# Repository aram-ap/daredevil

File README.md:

### Project Overview

A concise summary of the problem, goals, scope, and tools behind this project.

#### Problem Statement

A computer-vision based system which uses a depth camera and a set of vibration motors along each wrist to identify obstacles and help the visually impaired avoid physical dangers.

This project will utilize an Intel RealSense Depth Camera, NVIDIA Jetson Orin Nano, ESP32 microcontrollers, small vibration motors, and Batteries for its hardware. Software will be developed to utilize the camera system to identify obstacles. Vibration motors will change intensity and pattern for giving general direction and/or identify specific dangers.

#### Project Goals

The goal by the end of class is to have a working software + hardware proof of concept that can reliably detect obstacles, provide haptic feedback to nearest obstacles, utilize variable vibration intensities, and be fully wearable.

#### Scope of Work

This will be a self-contained device. Self-powered and can be ran completely isolated.

#### Tech Stack

TBD

#### Hardware

Hardware design files live in [`hardware/`](hardware/). All PCB work is done in **KiCad 10**, and enclosures are modeled in **Autodesk Fusion**. See the [hardware README](hardware/README.md) for full details.

```
hardware/
+-- README.md
+-- models/                        3D models for enclosures
|   +-- Wrist Module/
|       +-- Wrist_Module_Enclosure.f3z    Fusion archive (editable source)
|       +-- Wrist Module Enclosure.3mf    Print-ready model (open in a slicer)
|       +-- enclosure.png                 Assembled render
|       +-- enclosure_exploded.png        Exploded render
+-- wrist_module/                  KiCad project for the wrist haptic board
    +-- wrist_module.kicad_pro     Project file (open this in KiCad)
    +-- wrist_module.kicad_sch     Schematic
    +-- wrist_module.kicad_pcb     PCB layout
    +-- wrist_module.kicad_prl     Local KiCad UI settings (per user)
    +-- Prints/                    Exported schematic and board renders
    |   +-- wrist_module.pdf       Schematic (PDF)
    |   +-- wrist_schematic.png    Schematic (PNG, made from the PDF)
    |   +-- wrist_module.png       Front render
    |   +-- pcb_traces.png         PCB layout showing copper traces
    |   +-- wrist_module_back.png  Back render
    +-- Library/                   Third-party symbols and footprints
        +-- 113991054/             Seeed XIAO ESP32C3 symbol, footprint, and 3D model
        +-- OPL_Kicad_Library-master/  Seeed Open Parts Library
```

##### Wrist Module

The wrist module is a small battery-powered board worn on each wrist. It drives up to five vibration motors that signal the direction and type of nearby obstacles.

| Schematic | PCB (front) | PCB (traces) |
| --- | --- | --- |
|  |  |  |

| Part | Purpose |
| --- | --- |
| Seeed XIAO ESP32-C3 | Microcontroller; controls motor intensity and patterns |
| ULN2003A | Darlington driver array that switches the motors |
| 5 x motor connectors (MOT 1-5) | Vibration motor outputs, each with a 1N5819 flyback diode |
| Battery connector (BATT CONN) | Battery power input |
| PWR SW (SPDT) | Main power switch |
| TOGG BTN | User push button |
| PWR LED | Power indicator |

To open the project, open `hardware/wrist_module/wrist_module.kicad_pro` in KiCad 10. If symbols or footprints show as missing, add the libraries under `hardware/wrist_module/Library/` in **Preferences -> Manage Symbol/Footprint Libraries** (as project-specific libraries).

The board is housed in a two-part 3D-printed enclosure (base and lid, fastened with four cap screws that also hold the PCB). The lid has openings for the push button and power LED, and the base has side cutouts for the connectors and switch. The editable Fusion source (`.f3z`) and a print-ready `.3mf` are in [`hardware/models/Wrist Module/`](hardware/models/Wrist%20Module/).

| Enclosure (assembled) | Enclosure (exploded) |
| --- | --- |
|  |  |

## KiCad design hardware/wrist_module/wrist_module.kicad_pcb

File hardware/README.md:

# Hardware

Hardware design files for **DareDevil**, a wearable obstacle-detection system for the visually impaired. A depth camera and an NVIDIA Jetson Orin Nano detect obstacles, and a module on each wrist gives haptic feedback through vibration motors. See the [project README](../README.md) for the full overview.

All PCB work here is done in **KiCad 10**. Enclosures are modeled in **Autodesk Fusion** and exported for 3D printing.

**Author:** Aram Aprahamian ([aapraham@ucsc.edu](mailto:aapraham@ucsc.edu))

## Directory layout

```
hardware/
├── README.md
├── models/                        3D models for enclosures
│   └── Wrist Module/
│       ├── Wrist_Module_Enclosure.f3z    Fusion archive (editable source)
│       ├── Wrist Module Enclosure.3mf    Print-ready model (open in a slicer)
│       ├── enclosure.png                 Assembled render
│       └── enclosure_exploded.png        Exploded render
└── wrist_module/                  KiCad project for the wrist haptic board
    ├── wrist_module.kicad_pro     Project file (open this in KiCad)
    ├── wrist_module.kicad_sch     Schematic
    ├── wrist_module.kicad_pcb     PCB layout
    ├── wrist_module.kicad_prl     Local KiCad UI settings (per user)
    ├── Prints/                    Exported schematic and board renders
    │   ├── wrist_module.pdf       Schematic (PDF)
    │   ├── wrist_schematic.png    Schematic (PNG, made from the PDF)
    │   ├── wrist_module.png       Front render
    │   ├── pcb_traces.png         PCB layout showing copper traces
    │   └── wrist_module_back.png  Back render
    ├── Library/                   Third-party symbols and footprints
    │   ├── 113991054/             Seeed XIAO ESP32C3 symbol, footprint, and 3D model
    │   └── OPL_Kicad_Library-master/  Seeed Open Parts Library
```

## wrist_module

The wrist module is a small battery-powered board worn on each wrist. It drives up to five vibration motors that signal the direction and type of nearby obstacles.

| Schematic | PCB (front) | PCB (traces) |
| --- | --- | --- |
|  |  |  |

Main parts:

| Part | Purpose |
| --- | --- |
| Seeed XIAO ESP32-C3 | Microcontroller; controls motor intensity and patterns |
| ULN2003A | Darlington driver array that switches the motors |
| 5 x motor connectors (MOT 1–5) | Vibration motor outputs, each with a 1N5819 flyback diode |
| Battery connector (BATT CONN) | Battery power input |
| PWR SW (SPDT) | Main power switch |
| TOGG BTN | User push button |
| PWR LED | Power indicator |

### Enclosure

The board sits in a two-part 3D-printed enclosure: an open base and a flat lid, fastened together with four socket-head cap screws that also hold the PCB in place. The lid has openings for the push button (TOGG BTN) and the power LED, and the base has side cutouts for the board's connectors and switch.

| Assembled | Exploded |
| --- | --- |
|  |  |

- `models/Wrist Module/Wrist_Module_Enclosure.f3z`: editable source. Open it in Fusion with **File -> Open -> Open from my computer**.
- `models/Wrist Module/Wrist Module Enclosure.3mf`: print-ready model. Load it into a slicer (Bambu Studio, PrusaSlicer, Cura, etc.).

### Opening the project

1. Open `wrist_module/wrist_module.kicad_pro` in KiCad 10.
2. If symbols or footprints show as missing, add the libraries under `wrist_module/Library/` in **Preferences -> Manage Symbol/Footprint Libraries** (as project-specific libraries).

### Notes

- Everything in `Prints/` is exported from KiCad, and the enclosure renders and `.3mf` are exported from Fusion. Re-export them after changing the design so they stay current.
- To regenerate the schematic PNG from the PDF (needs ImageMagick and Ghostscript):
  `magick -density 300 wrist_module/Prints/wrist_module.pdf -background white -alpha remove -alpha off wrist_module/Prints/wrist_schematic.png`

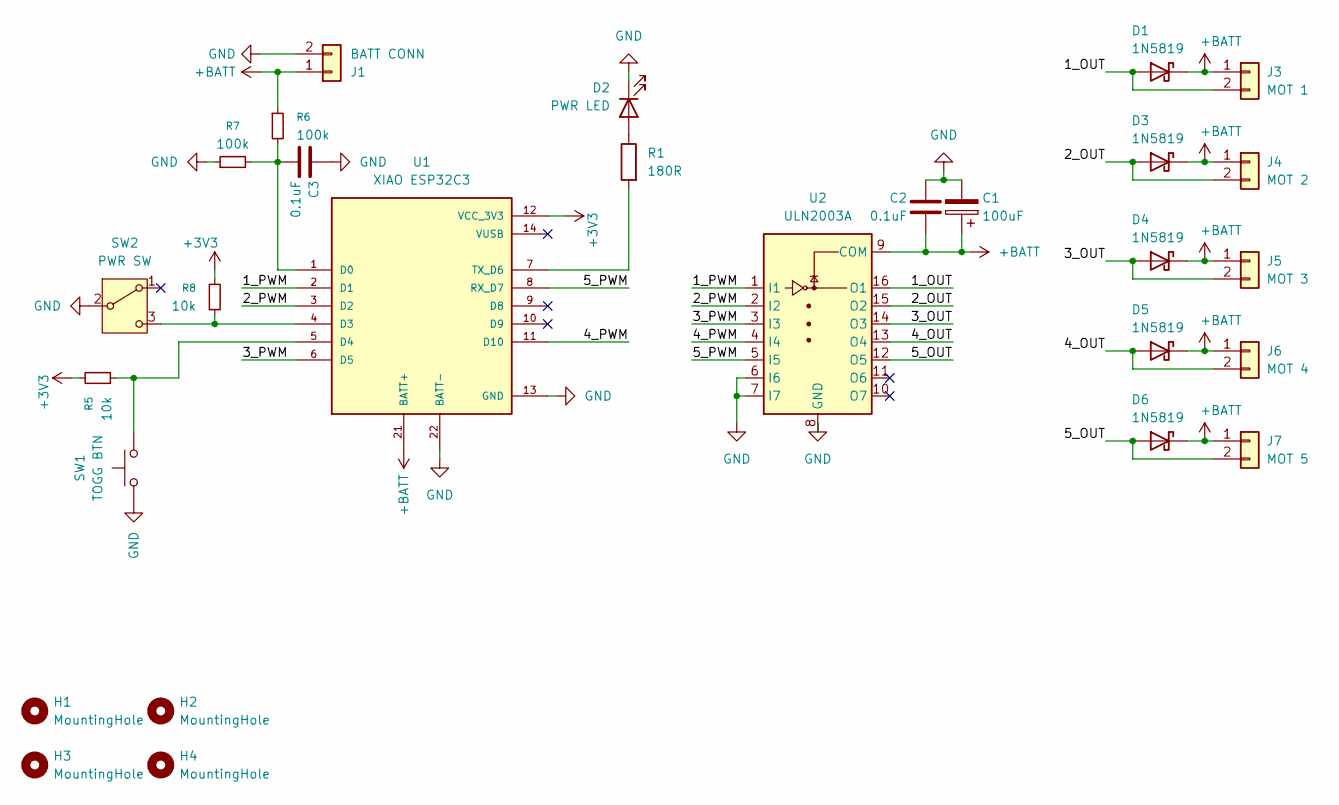
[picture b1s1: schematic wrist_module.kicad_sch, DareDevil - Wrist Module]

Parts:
C1: 100uF; CP_Radial_D8.0mm_P2.50mm
C2, C3: 0.1uF; C_Disc_D3.8mm_W2.6mm_P2.50mm
D1, D3, D4, D5, D6: 1N5819; D_DO-41_SOD81_P10.16mm_Horizontal
D2: PWR LED; LED_D5.0mm
H1, H2, H3, H4: MountingHole; MountingHole_2.2mm_M2_ISO7380
J1: BATT CONN; JST_PH_B2B-PH-K_1x02_P2.00mm_Vertical
J3: MOT 1; JST_PH_B2B-PH-K_1x02_P2.00mm_Vertical
J4: MOT 2; JST_PH_B2B-PH-K_1x02_P2.00mm_Vertical
J5: MOT 3; JST_PH_B2B-PH-K_1x02_P2.00mm_Vertical
J6: MOT 4; JST_PH_B2B-PH-K_1x02_P2.00mm_Vertical
J7: MOT 5; JST_PH_B2B-PH-K_1x02_P2.00mm_Vertical
R1: 180R; R_Axial_DIN0207_L6.3mm_D2.5mm_P7.62mm_Horizontal
R5, R8: 10k; R_Axial_DIN0207_L6.3mm_D2.5mm_P7.62mm_Horizontal
R6, R7: 100k; R_Axial_DIN0207_L6.3mm_D2.5mm_P7.62mm_Horizontal
SW1: TOGG BTN; SW_PUSH_6mm
SW2: PWR SW; JST_PH_B3B-PH-K_1x03_P2.00mm_Vertical
U1: XIAO ESP32C3; XIAO-ESP32-C3-DIP-SMD; PARTREV 23/05/2022
U2: ULN2003A; DIP-16_W7.62mm_LongPads

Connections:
+3V3: R5.2, R8.2, U1.12 (VCC_3V3)
+BATT: C1.1, C2.2, D1.1 (K), D3.1 (K), D4.1 (K), D5.1 (K), D6.1 (K), J1.1, J3.1, J4.1, J5.1, J6.1, J7.1, R6.1, U1.21 (BATT+), U2.9 (COM); also elsewhere on the board
/1_OUT: D1.2 (A), J3.2, U2.16 (O1)
/1_PWM: U1.2 (D1), U2.1 (I1)
/2_OUT: D3.2 (A), J4.2, U2.15 (O2)
/2_PWM: U1.3 (D2), U2.2 (I2)
/3_OUT: D4.2 (A), J5.2, U2.14 (O3)
/3_PWM: U1.6 (D5), U2.3 (I3)
/4_OUT: D5.2 (A), J6.2, U2.13 (O4)
/4_PWM: U1.11 (D10), U2.4 (I4)
/5_OUT: D6.2 (A), J7.2, U2.12 (O5)
/5_PWM: U1.8 (RX_D7), U2.5 (I5)
GND: C1.2, C2.1, C3.1, D2.1 (K), J1.2, R7.1, SW1.2, SW2.2 (B), U1.13 (GND), U1.22 (BATT-), U2.6 (I6), U2.7 (I7), U2.8 (GND); also elsewhere on the board
unnamed: D2.2 (A), R1.1
unnamed: R8.1, SW2.3 (C), U1.4 (D3)
unnamed: C3.2, R6.2, R7.2, U1.1 (D0)
unnamed: R5.1, SW1.1, U1.5 (D4)
unnamed: R1.2, U1.7 (TX_D6)

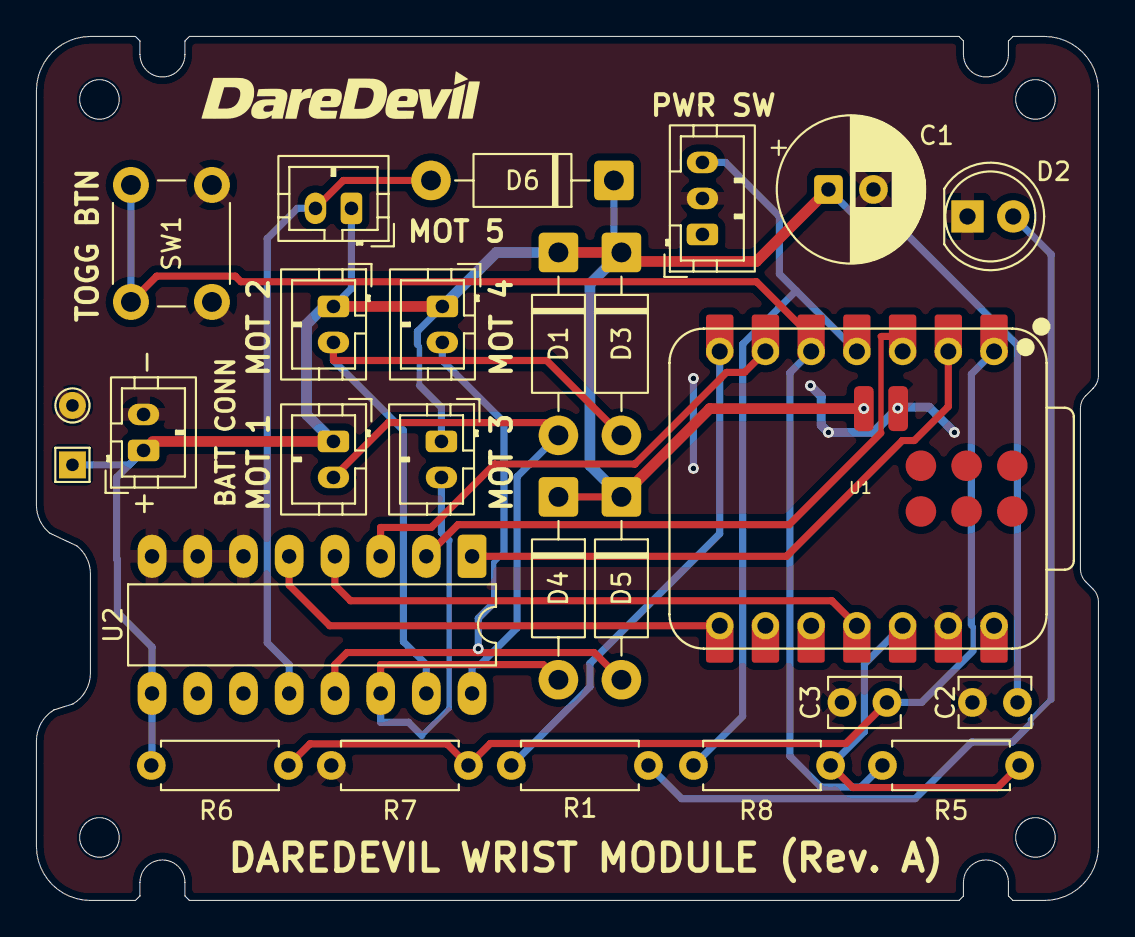
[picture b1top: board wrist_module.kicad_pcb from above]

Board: 2 copper layers, 59.0 x 48.0 mm, 30 parts (0 on the bottom side), 18 nets.

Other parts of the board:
T1: TestPoint_THTPad_1.5x1.5mm_Drill0.7mm
T2: TestPoint_THTPad_D1.5mm_Drill0.7mm

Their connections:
+BATT: T1.1; also elsewhere on the board
GND: T2.1; also elsewhere on the board

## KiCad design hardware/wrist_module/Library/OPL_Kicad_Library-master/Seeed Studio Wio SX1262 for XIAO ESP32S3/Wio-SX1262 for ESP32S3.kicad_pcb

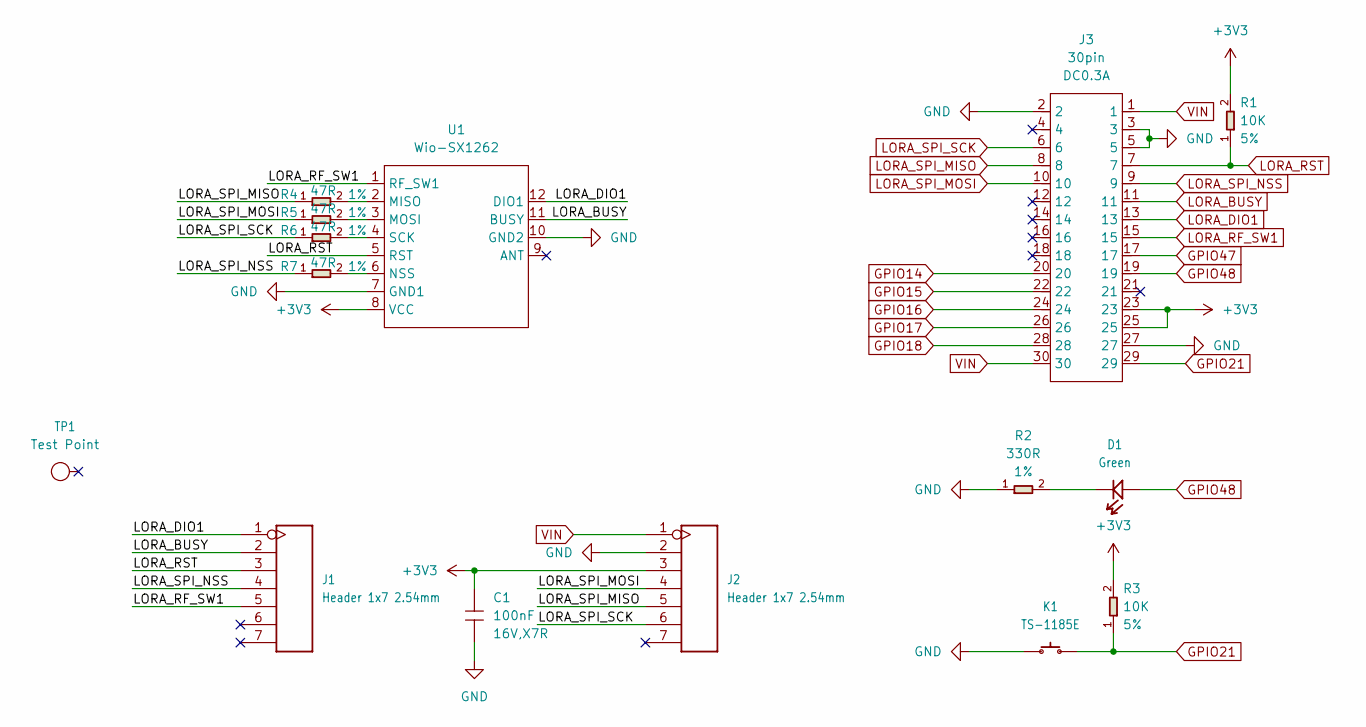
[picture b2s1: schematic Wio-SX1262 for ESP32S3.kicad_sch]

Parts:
C1: 100nF; C0402; Voltage Rating 16V,X7R; MPN CC0402KRX7R7BB104
D1: Green; LED-0603; MPN 19-217/G7C-AN1P2/3T
J1, J2: Header 1x7 2.54mm; H7-2.54; Part Type Header
J3: 30pin; BTB2X15-FEMALE-8.6X2.94X3.9MM; Rating DC0.3A; MPN BTB SCOKET P0.40
K1: TS-1185E; BUTTON2P_3_9X3X2MM; MPN TS-1185E
R1, R3: 10K; R0402; Power Rating 5%; MPN RC0402JR-0710KL
R2: 330R; R0402; Power Rating 1%; MPN RC0402FR-07330RL
R4, R5, R6, R7: 47R; R0402; Power Rating 1%; MPN RC0201FR-0745RL
TP1: Test Point; TP-D3_5c2_2mm; Part Type Test Point
U1: Wio-SX1262; MODULE12P-1.27-11X11.6MM; MPN Wio-SX1262

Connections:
+3V3: C1.1, J2.3, J3.23, J3.25, R1.2, R3.2, U1.8 (VCC)
GND: C1.2, J2.2, J3.2, J3.3, J3.5, J3.27, K1.1, R2.1, U1.7 (GND1), U1.10 (GND2)
GPIO14: J3.20
GPIO15: J3.22
GPIO16: J3.24
GPIO17: J3.26
GPIO18: J3.28
GPIO21: J3.29, K1.2, R3.1
GPIO47: J3.17
GPIO48: D1.1 (+), J3.19
LORA_BUSY: J1.2, J3.11, U1.11 (BUSY)
LORA_DIO1: J1.1, J3.13, U1.12 (DIO1)
LORA_RF_SW1: J1.5, J3.15, U1.1 (RF_SW1)
LORA_RST: J1.3, J3.7, R1.1, U1.5 (RST)
LORA_SPI_MISO: J2.5, J3.8, R4.1
LORA_SPI_MOSI: J2.4, J3.10, R5.1
LORA_SPI_NSS: J1.4, J3.9, R7.1
LORA_SPI_SCK: J2.6, J3.6, R6.1
unnamed: D1.2 (-), R2.2
unnamed: R4.2, U1.2 (MISO)
unnamed: R5.2, U1.3 (MOSI)
unnamed: R7.2, U1.6 (NSS)
unnamed: R6.2, U1.4 (SCK)
VIN: J2.1, J3.1, J3.30

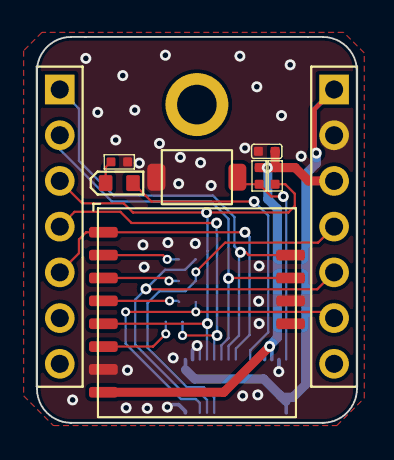
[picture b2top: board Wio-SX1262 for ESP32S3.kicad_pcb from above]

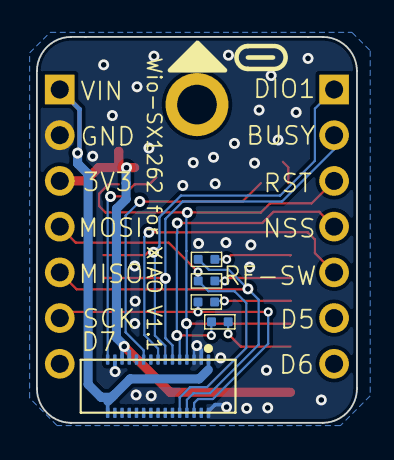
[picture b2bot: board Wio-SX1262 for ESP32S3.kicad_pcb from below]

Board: 2 copper layers, 17.8 x 21.4 mm, 15 parts (5 on the bottom side), 18 nets.
